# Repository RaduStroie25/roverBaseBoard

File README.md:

# roverBaseBoard
My Rover Project, too lazy to write another description. View documentation in the files. :P
STATUS: Unfinished

### Board Pins (Input)
These are the board pins that take input from the Microcontroller:
- 8x Digital pins. (for all motor driver direction control)
- 4x PWM or Analog pins. (for all motor speed control)
- 1x VCC pin (for driver logic voltage that can be 2.5V-5.5V)
- 1x Digital pin. (for driver Standby pins)
- 1x POWERLATCH pin (keep high while running)

### Board Pins (Output)
These are the pins that the board offers to a microcontroller:
- 1x Adjustable VCC power pin.
- 1x GND into the same source.
- 1x SCL (ina219)
- 1x SDA (ina219)

## Notes
- Measured TT motor max draw per motor 110mA-120mA. (without load or wheels on)
- do not run 75A through jumper cables... *

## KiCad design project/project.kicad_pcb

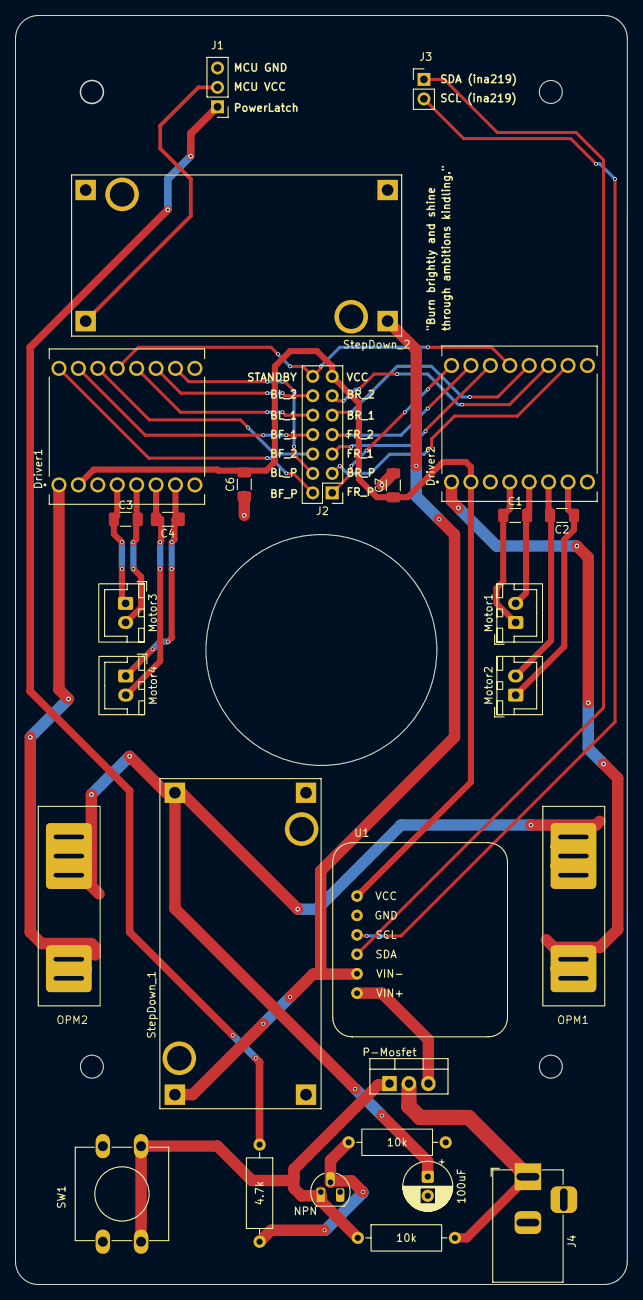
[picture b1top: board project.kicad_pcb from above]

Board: 2 copper layers, 80.0 x 166.0 mm, 28 parts (0 on the bottom side), 35 nets.

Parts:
4.7k: 4.7k; R_Axial_DIN0309_L9.0mm_D3.2mm_P12.70mm_Horizontal
10k, 10k#2: 10k; R_Axial_DIN0309_L9.0mm_D3.2mm_P12.70mm_Horizontal
100uF: 100uF; CP_Radial_D6.3mm_P2.50mm
C1, C2, C3, C4, C6, C7: 100nF; C_1206_3216Metric_Pad1.33x1.80mm_HandSolder
Driver1, Driver2: ROB-14450; MODULE_ROB-14450
J1: Conn_01x03; PinHeader_1x03_P2.54mm_Vertical
J2: Conn_02x07_Odd_Even; PinHeader_2x07_P2.54mm_Vertical
J3: Conn_01x02; PinHeader_1x02_P2.54mm_Vertical
J4: Barrel_Jack_Switch; BarrelJack_Horizontal
Motor1, Motor2, Motor3, Motor4: Conn_01x02_Pin; JST_XH_B2B-XH-A_1x02_P2.50mm_Vertical
NPN: NPN; TO-92_HandSolder
OPM1, OPM2: 1A; OPM_Kuoyuh_91
P-Mosfet: Q_PMOS_GDS; TO-220-3_Vertical
SW1: SW_Push; SW_PUSH-12mm
StepDown_1, StepDown_2: LM2596_Module; CONV_MC00100
U1: module_ina219

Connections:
/PowLatch: 4.7k.1, J1.1
/STANDBY: Driver1.13 (STBY), Driver2.13 (STBY), J2.14
/VCC: C6.2, C7.1, Driver1.2 (VCC), Driver2.2 (VCC), J2.13, U1.1 (VCC)
/VM: 100uF.1, OPM1.2 (B), OPM2.2 (B), StepDown_1.OUT+
GND: 10k#2.1, 100uF.2, C6.1, C7.2, Driver1.3 (GND), Driver1.8 (GND), Driver1.9 (GND), Driver2.3 (GND), Driver2.8 (GND), Driver2.9 (GND), J1.3, J4.2, J4.3, NPN.3 (E), SW1.1, StepDown_1.IN-, StepDown_1.OUT-, StepDown_2.IN-, StepDown_2.OUT-, U1.2 (GND)
unnamed: C3.1, Driver1.4 (A01), Motor3.1
unnamed: C3.2, Driver1.5 (A02), Motor3.2
unnamed: Driver1.14 (AI1), J2.6
unnamed: Driver1.15 (AI2), J2.8
unnamed: C4.1, Driver1.7 (B01), Motor4.1
unnamed: C4.2, Driver1.6 (B02), Motor4.2
unnamed: Driver1.12 (BI1), J2.10
unnamed: Driver1.11 (BI2), J2.12
unnamed: Driver1.16 (PWMA), J2.2
unnamed: Driver1.10 (PWMB), J2.4
unnamed: Driver1.1 (VM), OPM2.1 (A)
unnamed: C1.1, Driver2.4 (A01), Motor1.1
unnamed: C1.2, Driver2.5 (A02), Motor1.2
unnamed: Driver2.14 (AI1), J2.5
unnamed: Driver2.15 (AI2), J2.7
unnamed: C2.1, Driver2.7 (B01), Motor2.1
unnamed: C2.2, Driver2.6 (B02), Motor2.2
unnamed: Driver2.12 (BI1), J2.9
unnamed: Driver2.11 (BI2), J2.11
unnamed: Driver2.16 (PWMA), J2.1
unnamed: Driver2.10 (PWMB), J2.3
unnamed: Driver2.1 (VM), OPM1.1 (A)
unnamed: J1.2, StepDown_2.OUT+
unnamed: J3.1, U1.4 (SDA)
unnamed: J3.2, U1.3 (SCL)
unnamed: 10k.2, J4.1, P-Mosfet.2 (D)
unnamed: 10k.1, NPN.1 (C), P-Mosfet.1 (G), SW1.2
unnamed: P-Mosfet.3 (S), U1.6 (VIN+)
unnamed: 4.7k.2, 10k#2.2, NPN.2 (B)
unnamed: StepDown_1.IN+, StepDown_2.IN+, U1.5 (VIN-)
